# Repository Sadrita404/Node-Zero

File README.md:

<div align="center">
  <table border="0" cellpadding="0" cellspacing="0">
    <tr>
      <td align="center" style="background: #ffffff; border: 1px solid #d0d7de; border-radius: 12px; padding: 16px; box-shadow: 0 4px 12px rgba(0,0,0,0.05);">
        
        <div style="margin-top: 12px; font-family: -apple-system, BlinkMacSystemFont, 'Segoe UI', Helvetica, Arial, sans-serif; font-size: 13px; color: #57606a; font-weight: 500;">
      </td>
    </tr>
  </table>
</div>

| Title | Node Zero |
| :-- | :---|
|Author |Sadrita Neogi|

## What's this?

Node Zero is an  rp2040 based micro-controller unit that consist of the rp2040 micro processor, the 16Mbit SPI NOR Flash, a crystal oscillator that synchronizes communication in the board between the USB abd rp2040, a voltage regulator, reset and boot switch.

## Why I built it ?

This is the starter project of stasis and I have not make any dev board ever before, so this is my the first time I am making an dev board so I am very excited to build this. That's why I am making the PCB whole custom thing. I have also get help from the detailed guide that is provided on the stasis website.

<div align="center">

| | PCB Designing | |
| :---: | :---: | :---: |
|  |  |  |
|  |  |  |
|  |  |  |

<div align="center">
  <h2> Final Look </h2>
  <table border="0" cellpadding="10" cellspacing="0" style="border-collapse: collapse;">
    <tr>
      <!-- FRONT SIDE CARD -->
      <td align="center" valign="top" width="50%" style="background: #ffffff; border: 1px solid #d0d7de; border-radius: 12px; padding: 16px; box-shadow: 0 4px 12px rgba(0,0,0,0.05);">
        
        <div style="margin-top: 12px; font-family: -apple-system, BlinkMacSystemFont, 'Segoe UI', Helvetica, Arial, sans-serif; font-size: 13px; color: #57606a; font-weight: 600; text-transform: uppercase; letter-spacing: 0.5px;">
          ▲ Front Side View
        </div>
      </td>
      <!-- SPACER FOR GITHUB MOBILE DEGRADATION -->
      <td width="2%">&nbsp;</td>
      <!-- BACK SIDE CARD -->
      <td align="center" valign="top" width="50%" style="background: #ffffff; border: 1px solid #d0d7de; border-radius: 12px; padding: 16px; box-shadow: 0 4px 12px rgba(0,0,0,0.05);">
        
        <div style="margin-top: 12px; font-family: -apple-system, BlinkMacSystemFont, 'Segoe UI', Helvetica, Arial, sans-serif; font-size: 13px; color: #57606a; font-weight: 600; text-transform: uppercase; letter-spacing: 0.5px;">
          ▲ Back Side View
        </div>
      </td>
    </tr>
  </table>
</div>
</div>

<div align="center">
  <h2> Bill of Materials </h2>
</div>

| Name | Purpose | Qty | Total (USD) | Link | Distributor |
| :--- | :--- | :---: | :---: | :---: | :--- |
| C9,C12 | 1uF 10V X5R ±10% 0402 MLCC | 20 | 0.1220 | [Link](https://lcsc.com/product-detail/C14445.html) | JLCPCB |
| C10,C11,C5,C8,C3,C2,C7,C6,C4,C17,C1,C20,C18 | 0.1uF (100nF) 16V X7R ±10% 0402 MLCC | 75 | 0.5775 | [Link](https://lcsc.com/product-detail/C1525.html) | JLCPCB |
| C13,C14 | 10uF 25V X5R ±10% 0805 MLCC | 20 | 4.3840 | [Link](https://lcsc.com/product-detail/C15850.html) | JLCPCB |
| C16,C15 | 33pF 50V C0G ±5% 0402 MLCC | 20 | 0.1160 | [Link](https://lcsc.com/product-detail/C1562.html) | JLCPCB |
| C19 | 10nF 50V X7R ±10% 0402 MLCC | 20 | 0.1740 | [Link](https://lcsc.com/product-detail/C15195.html) | JLCPCB |
| C21 | 2.2uF 6.3V X5R ±20% 0402 MLCC | 20 | 0.1660 | [Link](https://lcsc.com/product-detail/C12530.html) | JLCPCB |
| D3,D1,D2 | Red Water Clear 0603 LED Indication | 25 | 0.1800 | [Link](https://lcsc.com/product-detail/C2286.html) | JLCPCB |
| J1 | USB Type-C Receptacle 16P Female SMD R/A | 5 | 0.9170 | [Link](https://lcsc.com/product-detail/C165948.html) | JLCPCB |
| R2,R1 | 5.1kΩ 50V 62.5mW Thick Film Resistor ±1% 0402 | 20 | 0.0200 | [Link](https://lcsc.com/product-detail/C25905.html) | JLCPCB |
| R4,R3 | 30Ω 50V 62.5mW Thick Film Resistor ±5% 0402 | 20 | 0.0240 | [Link](https://lcsc.com/product-detail/C137883.html) | JLCPCB |
| R5,R7 | 1kΩ 50V 62.5mW Thick Film Resistor ±1% 0402 | 20 | 0.0820 | [Link](https://lcsc.com/product-detail/C11702.html) | JLCPCB |
| R6 | 10kΩ 50V 62.5mW Thick Film Resistor ±1% 0402 | 20 | 0.0640 | [Link](https://lcsc.com/product-detail/C25744.html) | JLCPCB |
| R10,R9,R8 | 470Ω 50V 62.5mW Thick Film Resistor ±1% 0402 | 25 | 0.0300 | [Link](https://lcsc.com/product-detail/C25117.html) | JLCPCB |
| SW1 | Tactile Switches 12V 50mA Black Button SMD SPST | 9 | 0.4950 | [Link](https://lcsc.com/product-detail/C720477.html) | JLCPCB |
| U1 | RP2040 Microcontroller (MCU) 133MHz LQFN-56 | 5 | 4.9045 | [Link](https://lcsc.com/product-detail/C2040.html) | JLCPCB |
| U2 | MCP1700T-3302E/TT Fixed 3.3V 250mA Linear LDO | 5 | 2.1595 | [Link](https://lcsc.com/product-detail/C39051.html) | JLCPCB |
| U3 | W25Q16JVUXIQ 16Mbit 133MHz SPI NOR FLASH USON-8 | 5 | 7.8745 | [Link](https://lcsc.com/product-detail/C2843335.html) | JLCPCB |
| U4 | ICM-20608-G 6-Axis IMU Accel + Gyro LGA-16 | 2 | 26.3282 | [Link](https://lcsc.com/product-detail/C78569.html) | JLCPCB |
| Y1 | 12MHz 20pF Crystal Oscillator SMD3225-4P | 7 | 0.6972 | [Link](https://lcsc.com/product-detail/C9002.html) | JLCPCB |
| PCB Fabrication (Node_Zero)	| 2-layer PCB — the board itself| 	5	| $2.00 |	—	 | JLCPCB |
| PCBA SMT Assembly|	SMT assembly of all SMD components| 	2| 	$41.63	| —	| JLCPCB |
| Shipping PCB	| E- Post (Cheapest) | 	- |	$11.74	| — | 	JLCPCB |
| Total |    |     |   $104.69    |   |    |   |

The project budget is $100 and my BOM is a $4 over that right now. But since I already have another project approved (a PCB business card),and I  order them both together that will cut down on shipping costs and bring the total under $100.

Also, this is my first time building a dev board and I don't have any experience soldering SMD components. Since I don't own a hot plate,So I wouldn't be able to assemble it manually myself and finish the project. So, to stay within that $100 budget, I'm going with PCB assembly instead.

#### Please approve this project it's my first devboard ....

**Project Under Hack Club**

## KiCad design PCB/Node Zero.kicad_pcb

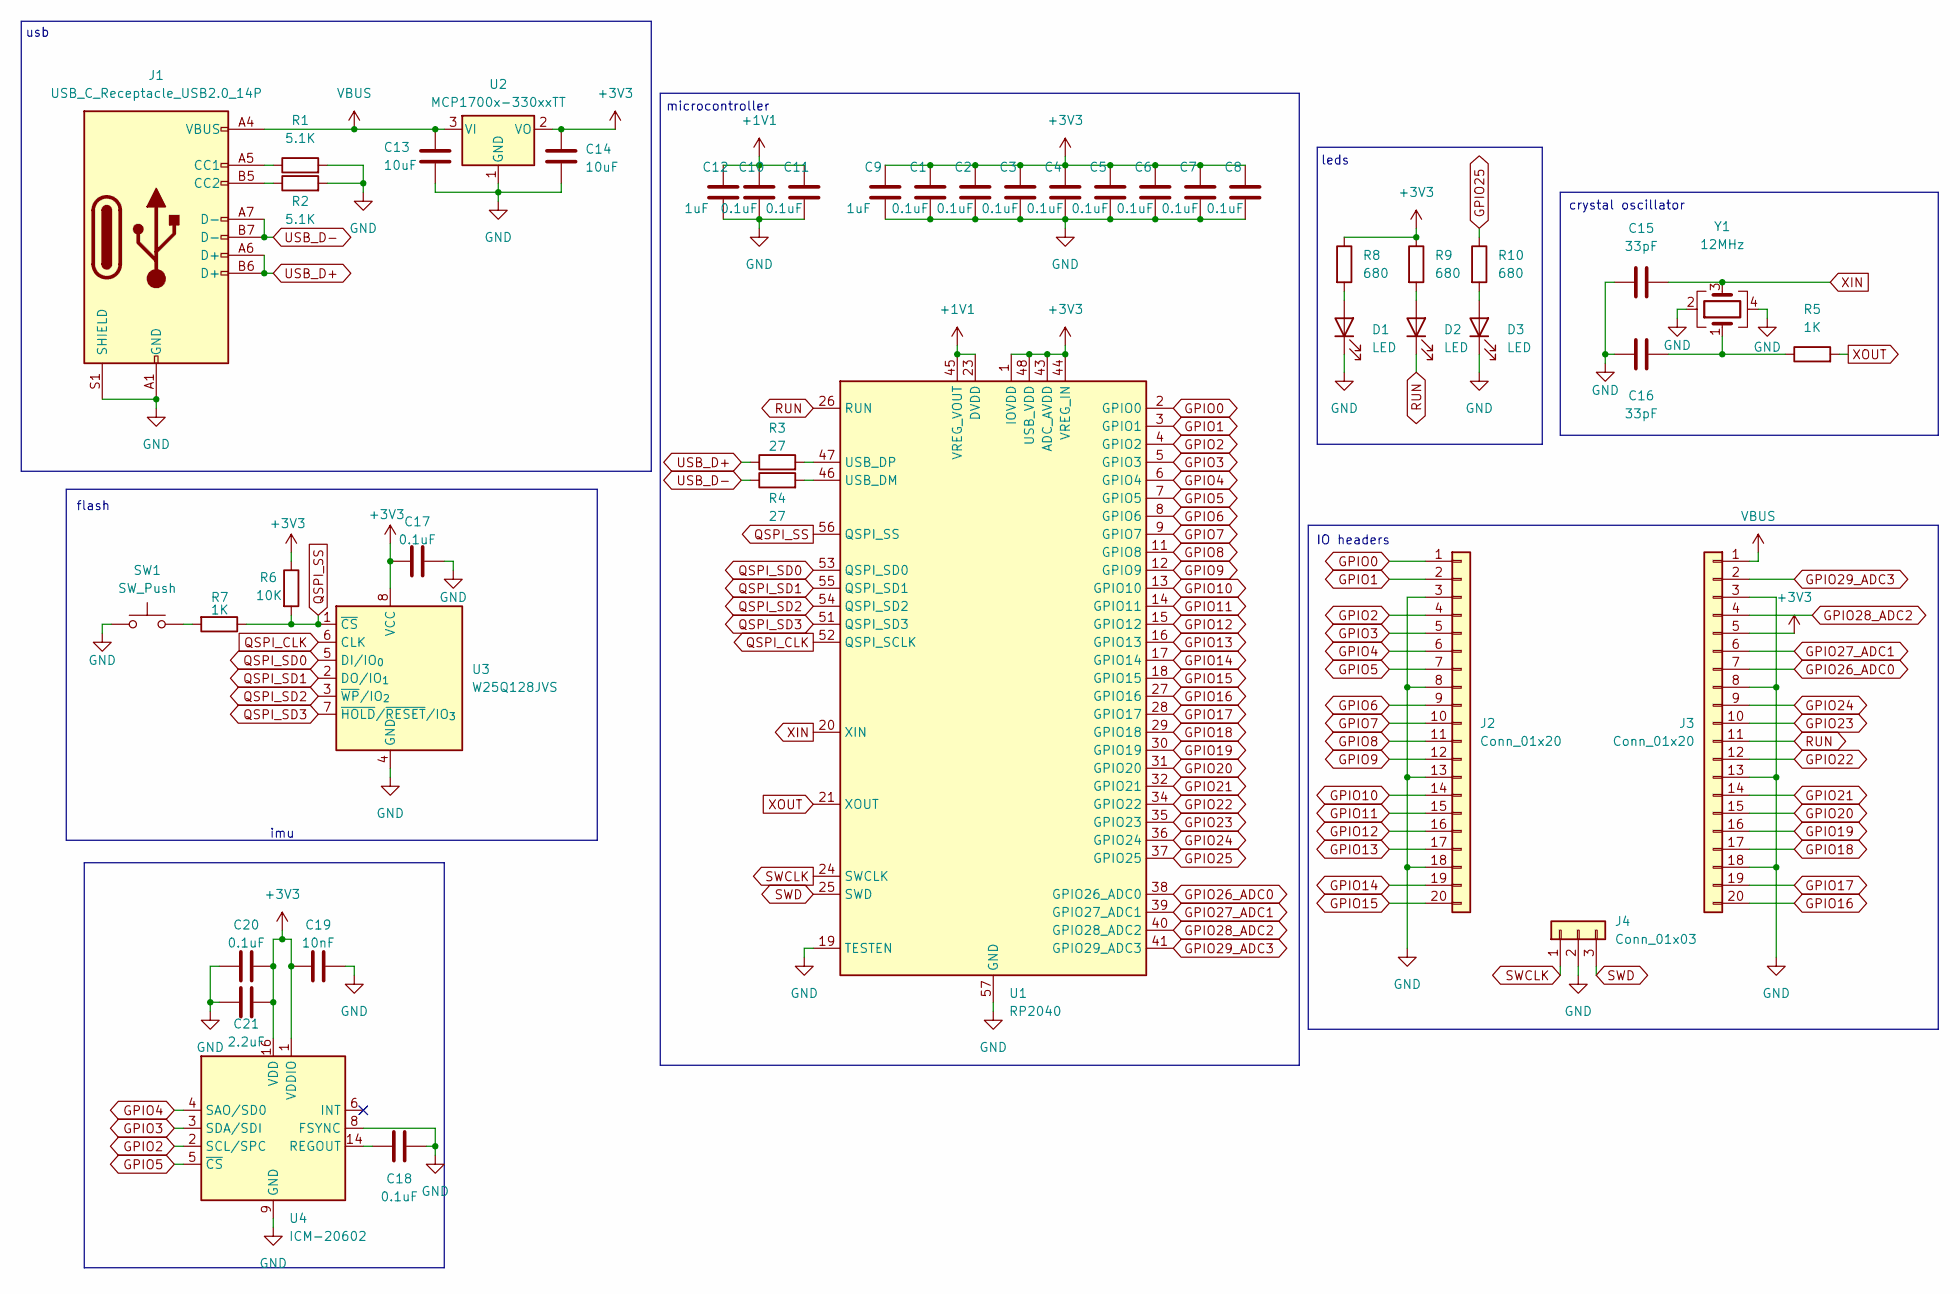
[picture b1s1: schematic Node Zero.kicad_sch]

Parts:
C1, C2, C3, C4, C5, C6, C7, C8, C10, C11, C17, C18, C20: 0.1uF; C_0402_1005Metric
C9, C12: 1uF; C_0402_1005Metric
C13, C14: 10uF; C_0603_1608Metric
C15, C16: 33pF; C_0402_1005Metric
C19: 10nF; C_0402_1005Metric
C21: 2.2uF; C_0402_1005Metric
D1, D2, D3: LED; LED_0603_1608Metric
J1: USB_C_Receptacle_USB2.0_14P; USB_C_Receptacle_HRO_TYPE-C-31-M-12
J2, J3: Conn_01x20; PinHeader_1x20_P2.54mm_Vertical
J4: Conn_01x03; PinHeader_1x03_P2.54mm_Vertical
R1, R2: 5.1K; R_0402_1005Metric
R3, R4: 27; R_0402_1005Metric
R5, R7: 1K; R_0402_1005Metric
R6: 10K; R_0402_1005Metric
R8, R9, R10: 680; R_0402_1005Metric
SW1: SW_Push; SW_Push_SPST_NO_Alps_SKRK
U1: RP2040; QFN-56-1EP_7x7mm_P0.4mm_EP3.2x3.2mm
U2: MCP1700x-330xxTT; SOT-23
U3: W25Q128JVS; Winbond_USON-8-1EP_3x2mm_P0.5mm_EP0.2x1.6mm
U4: ICM-20602; LGA-16_3x3mm_P0.5mm_LayoutBorder3x5y
Y1: 12MHz; Crystal_SMD_3225-4Pin_3.2x2.5mm

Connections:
+1V1: C10.1, C11.1, C12.1, U1.23 (DVDD), U1.45 (VREG_VOUT), U1.50 (DVDD)
+3V3: C1.1, C2.1, C3.1, C4.1, C5.1, C6.1, C7.1, C8.1, C9.1, C14.1, C17.1, C19.1, C20.2, C21.2, J3.5, R6.1, R8.1, R9.1, U1.1 (IOVDD), U1.10 (IOVDD), U1.22 (IOVDD), U1.33 (IOVDD), U1.42 (IOVDD), U1.43 (ADC_AVDD), U1.44 (VREG_IN), U1.48 (USB_VDD), U1.49 (IOVDD), U2.2 (VO), U3.8 (VCC), U4.1 (VDDIO), U4.16 (VDD)
GND: C1.2, C2.2, C3.2, C4.2, C5.2, C6.2, C7.2, C8.2, C9.2, C10.2, C11.2, C12.2, C13.2, C14.2, C15.1, C16.1, C17.2, C18.2, C19.2, C20.1, C21.1, D1.1 (K), D3.1 (K), J1.A1 (GND), J1.A12 (GND), J1.B1 (GND), J1.B12 (GND), J1.S1 (SHIELD), J2.3, J2.8, J2.13, J2.18, J3.3, J3.8, J3.13, J3.18, J4.2, R1.2, R2.2, SW1.1, U1.19 (TESTEN), U1.57 (GND), U2.1 (GND), U3.4 (GND), U4.8 (FSYNC), U4.9 (GND), U4.10 (GND), U4.11 (GND), U4.12 (GND), U4.13 (GND), U4.15 (GND), Y1.2, Y1.4
GPIO0: J2.1, U1.2 (GPIO0)
GPIO1: J2.2, U1.3 (GPIO1)
GPIO2: J2.4, U1.4 (GPIO2), U4.2 (SCL/SPC)
GPIO3: J2.5, U1.5 (GPIO3), U4.3 (SDA/SDI)
GPIO4: J2.6, U1.6 (GPIO4), U4.4 (SAO/SD0)
GPIO5: J2.7, U1.7 (GPIO5), U4.5 (~CS)
GPIO6: J2.9, U1.8 (GPIO6)
GPIO7: J2.10, U1.9 (GPIO7)
GPIO8: J2.11, U1.11 (GPIO8)
GPIO9: J2.12, U1.12 (GPIO9)
GPIO10: J2.14, U1.13 (GPIO10)
GPIO11: J2.15, U1.14 (GPIO11)
GPIO12: J2.16, U1.15 (GPIO12)
GPIO13: J2.17, U1.16 (GPIO13)
GPIO14: J2.19, U1.17 (GPIO14)
GPIO15: J2.20, U1.18 (GPIO15)
GPIO16: J3.20, U1.27 (GPIO16)
GPIO17: J3.19, U1.28 (GPIO17)
GPIO18: J3.17, U1.29 (GPIO18)
GPIO19: J3.16, U1.30 (GPIO19)
GPIO20: J3.15, U1.31 (GPIO20)
GPIO21: J3.14, U1.32 (GPIO21)
GPIO22: J3.12, U1.34 (GPIO22)
GPIO23: J3.10, U1.35 (GPIO23)
GPIO24: J3.9, U1.36 (GPIO24)
GPIO25: R10.1, U1.37 (GPIO25)
GPIO26_ADC0: J3.7, U1.38 (GPIO26_ADC0)
GPIO27_ADC1: J3.6, U1.39 (GPIO27_ADC1)
GPIO28_ADC2: J3.4, U1.40 (GPIO28_ADC2)
GPIO29_ADC3: J3.2, U1.41 (GPIO29_ADC3)
unnamed: C16.2, R5.1, Y1.1
unnamed: D1.2 (A), R8.2
unnamed: D2.2 (A), R9.2
unnamed: D3.2 (A), R10.2
unnamed: J1.A5 (CC1), R1.1
unnamed: J1.B5 (CC2), R2.1
unnamed: R7.2, SW1.2
unnamed: R4.2, U1.46 (USB_DM)
unnamed: R3.2, U1.47 (USB_DP)
unnamed: C18.1, U4.14 (REGOUT)
QSPI_CLK: U1.52 (QSPI_SCLK), U3.6 (CLK)
QSPI_SD0: U1.53 (QSPI_SD0), U3.5 (DI/IO_{0})
QSPI_SD1: U1.55 (QSPI_SD1), U3.2 (DO/IO_{1})
QSPI_SD2: U1.54 (QSPI_SD2), U3.3 (~WP/IO_{2})
QSPI_SD3: U1.51 (QSPI_SD3), U3.7 (~HOLD/~RESET/IO_{3})
QSPI_SS: R6.2, R7.1, U1.56 (QSPI_SS), U3.1 (~CS)
RUN: D2.1 (K), J3.11, U1.26 (RUN)
SWCLK: J4.1, U1.24 (SWCLK)
SWD: J4.3, U1.25 (SWD)
USB_D+: J1.A6 (D+), J1.B6 (D+), R3.1
USB_D-: J1.A7 (D-), J1.B7 (D-), R4.1
VBUS: C13.1, J1.A4 (VBUS), J1.A9 (VBUS), J1.B4 (VBUS), J1.B9 (VBUS), J3.1, U2.3 (VI)
XIN: C15.2, U1.20 (XIN), Y1.3
XOUT: R5.2, U1.21 (XOUT)

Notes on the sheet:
leds
microcontroller
crystal oscillator
usb
IO headers
flash
imu

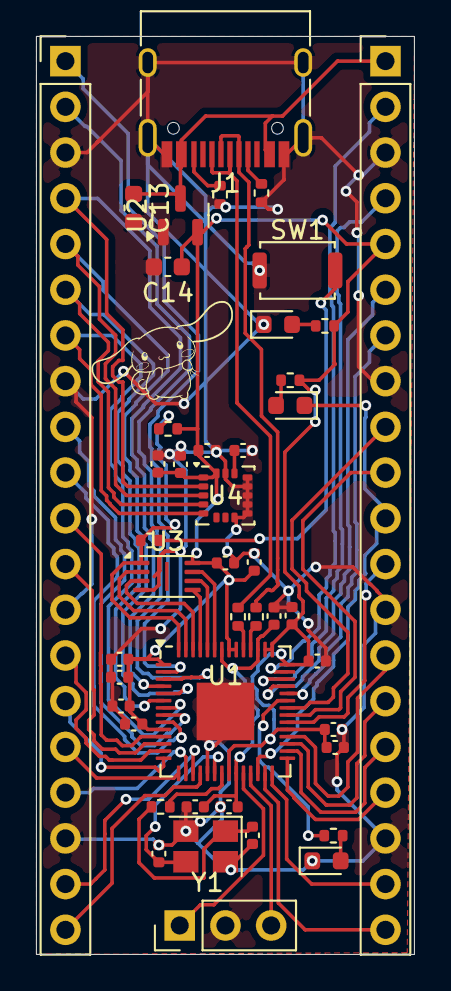
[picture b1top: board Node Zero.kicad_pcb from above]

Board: 2 copper layers, 21.0 x 51.0 mm, 44 parts (0 on the bottom side), 57 nets.

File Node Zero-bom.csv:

Name,Purpose,Quantity,Total Cost (USD),Link,Distributor
"PCBA SMT Assembly","SMT assembly of all SMD components",2,41.63,"","JLCPCB"
"C10,C11,C5,C8,C3,C2,C7,C6,C4,C17,C1,C20,C18","0.1uF (100nF) 16V X7R ±10% 0402 MLCC",75,0.58,"https://lcsc.com/product-detail/C1525.html","JLCPCB"
"C13,C14","10uF 25V X5R ±10% 0805 MLCC",20,4.38,"https://lcsc.com/product-detail/C15850.html","JLCPCB"
"C16,C15","33pF 50V C0G ±5% 0402 MLCC",20,0.12,"https://lcsc.com/product-detail/C1562.html","JLCPCB"
"C19","10nF 50V X7R ±10% 0402 MLCC",20,0.17,"https://lcsc.com/product-detail/C15195.html","JLCPCB"
"C21","2.2uF 6.3V X5R ±20% 0402 MLCC",20,0.17,"https://lcsc.com/product-detail/C12530.html","JLCPCB"
"D3,D1,D2","Red Water Clear 0603 LED Indication",25,0.18,"https://lcsc.com/product-detail/C2286.html","JLCPCB"
"J1","USB Type-C Receptacle 16P Female SMD R/A",5,0.92,"https://lcsc.com/product-detail/C165948.html","JLCPCB"
"R2,R1","5.1kΩ 50V 62.5mW Thick Film Resistor ±1% 0402",20,0.02,"https://lcsc.com/product-detail/C25905.html","JLCPCB"
"R4,R3","30Ω 50V 62.5mW Thick Film Resistor ±5% 0402",20,0.02,"https://lcsc.com/product-detail/C137883.html","JLCPCB"
"C9,C12","1uF 10V X5R ±10% 0402 MLCC",20,0.12,"https://lcsc.com/product-detail/C14445.html","JLCPCB"
"R6","10kΩ 50V 62.5mW Thick Film Resistor ±1% 0402",20,0.06,"https://lcsc.com/product-detail/C25744.html","JLCPCB"
"R10,R9,R8","470Ω 50V 62.5mW Thick Film Resistor ±1% 0402",25,0.03,"https://lcsc.com/product-detail/C25117.html","JLCPCB"
"SW1","Tactile Switches 12V 50mA Black Button SMD SPST",9,0.49,"https://lcsc.com/product-detail/C720477.html","JLCPCB"
"U1","RP2040 Microcontroller (MCU) 133MHz LQFN-56",5,4.90,"https://lcsc.com/product-detail/C2040.html","JLCPCB"
"U2","MCP1700T-3302E/TT Fixed 3.3V 250mA Linear LDO",5,2.16,"https://lcsc.com/product-detail/C39051.html","JLCPCB"
"U3","W25Q16JVUXIQ 16Mbit 133MHz SPI NOR FLASH USON-8",5,7.87,"https://lcsc.com/product-detail/C2843335.html","JLCPCB"
"U4","ICM-20608-G 6-Axis IMU Accel + Gyro LGA-16",2,26.33,"https://lcsc.com/product-detail/C78569.html","JLCPCB"
"Y1","12MHz 20pF Crystal Oscillator SMD3225-4P",7,0.70,"https://lcsc.com/product-detail/C9002.html","JLCPCB"
"PCB Fabrication (Node_Zero)","2-layer PCB — the board itself",5,2.00,"","JLCPCB"
"R5,R7","1kΩ 50V 62.5mW Thick Film Resistor ±1% 0402",20,0.08,"https://lcsc.com/product-detail/C11702.html","JLCPCB"

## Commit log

2026-06-28 Fix total cost formatting in README
    Adjusted total cost formatting in the BOM section.
